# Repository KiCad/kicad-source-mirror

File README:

= KiCad GUI translations

This is the repository for the po files that is used for the GUI
translations for KiCad.

It is cmake equipped to conform with the rest of the installation
principles for KiCad.

== Depends
- Cmake
- Gettext

== How to install
```
cd kicad-i18n
cmake .
make
make install
```

If you want to change the default install prefix to match your KiCad
build, you can add for
example use `-DCMAKE_INSTALL_PREFIX=/usr`.

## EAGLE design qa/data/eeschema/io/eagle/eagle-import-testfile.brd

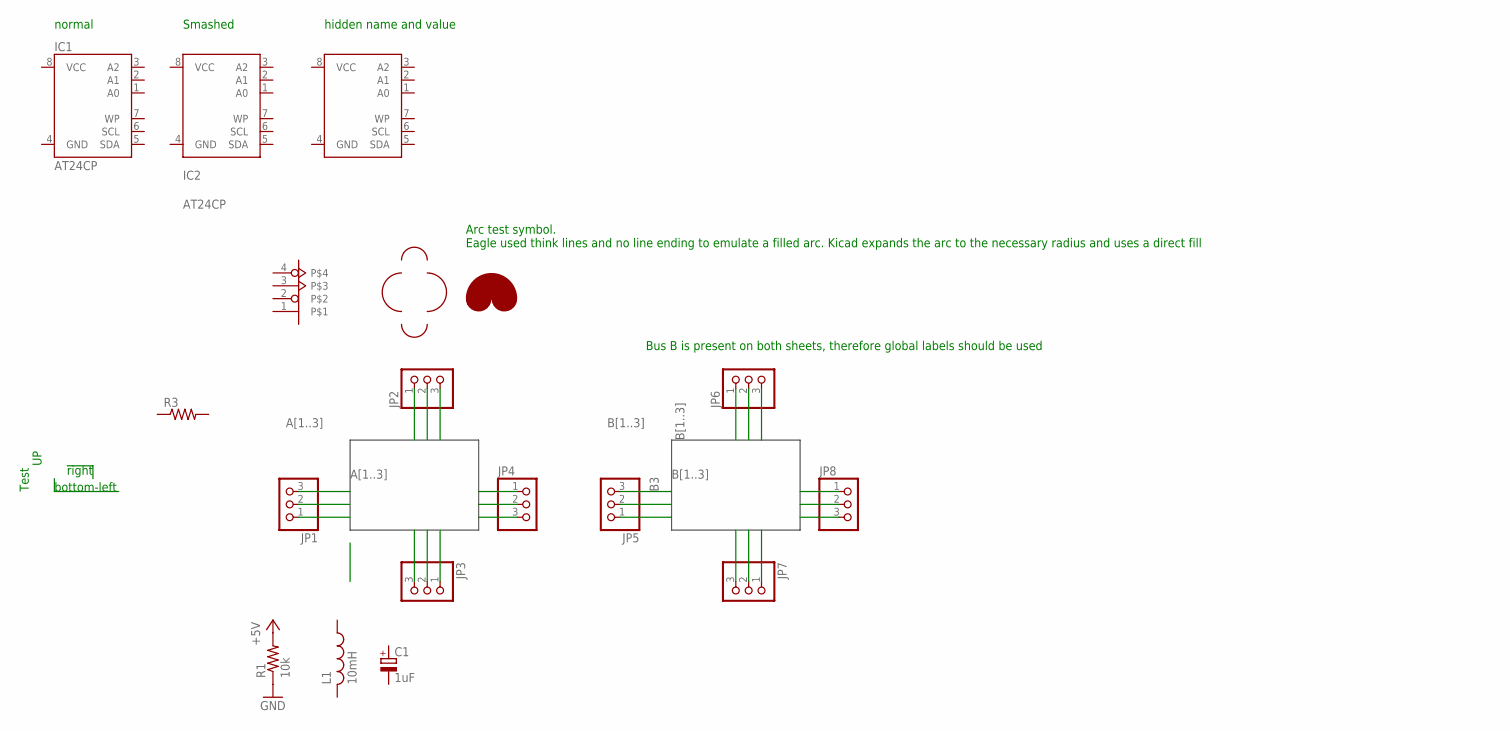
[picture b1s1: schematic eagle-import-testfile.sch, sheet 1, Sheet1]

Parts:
C1: 1uF; 085CS_1AR
IC1, IC2, IC3: AT24CP; DIL08
JP1, JP2, JP3, JP4, JP5, JP6, JP7, JP8: PINHD-1X3; 1X03
L1: 10mH; L2012C
R1: 10k; R0603
R3: R-US_0204/2V; 0204V
U$2: PINSHAPETEST; 1X04

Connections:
+5V: R1.2
A1: JP1.1, JP2.1, JP3.1, JP4.1
A2: JP1.2, JP2.2, JP3.2, JP4.2
A3: JP1.3, JP2.3, JP3.3, JP4.3
B1: JP5.1, JP6.1, JP7.3, JP8.1; also elsewhere on the board
B2: JP5.2, JP6.2, JP7.2, JP8.2; also elsewhere on the board
B3: JP5.3, JP6.3, JP7.1, JP8.3; also elsewhere on the board
GND: IC1.4 (GND), IC2.4 (GND), IC3.4 (GND), R1.1
VCC: IC1.8 (VCC), IC2.8 (VCC), IC3.8 (VCC)

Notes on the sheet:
right
Test
bottom-left
Bus B is present on both sheets, therefore global labels should be used
Arc test symbol. Eagle used think lines and no line ending to emulate a filled arc. Kicad expands the arc to the necessary radius and uses a direct fill
normal
Smashed
hidden name and value

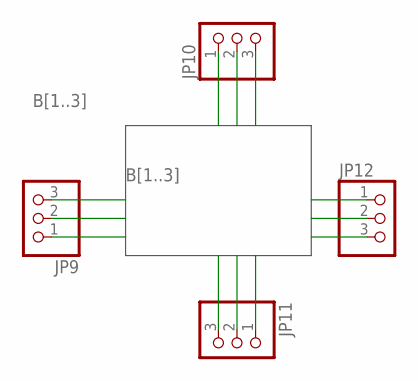
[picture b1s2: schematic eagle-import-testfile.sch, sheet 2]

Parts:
JP9, JP10, JP11, JP12: PINHD-1X3; 1X03

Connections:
B1: JP9.1, JP10.1, JP11.3, JP12.1; also elsewhere on the board
B2: JP9.2, JP10.2, JP11.2, JP12.2; also elsewhere on the board
B3: JP9.3, JP10.3, JP11.1, JP12.3; also elsewhere on the board

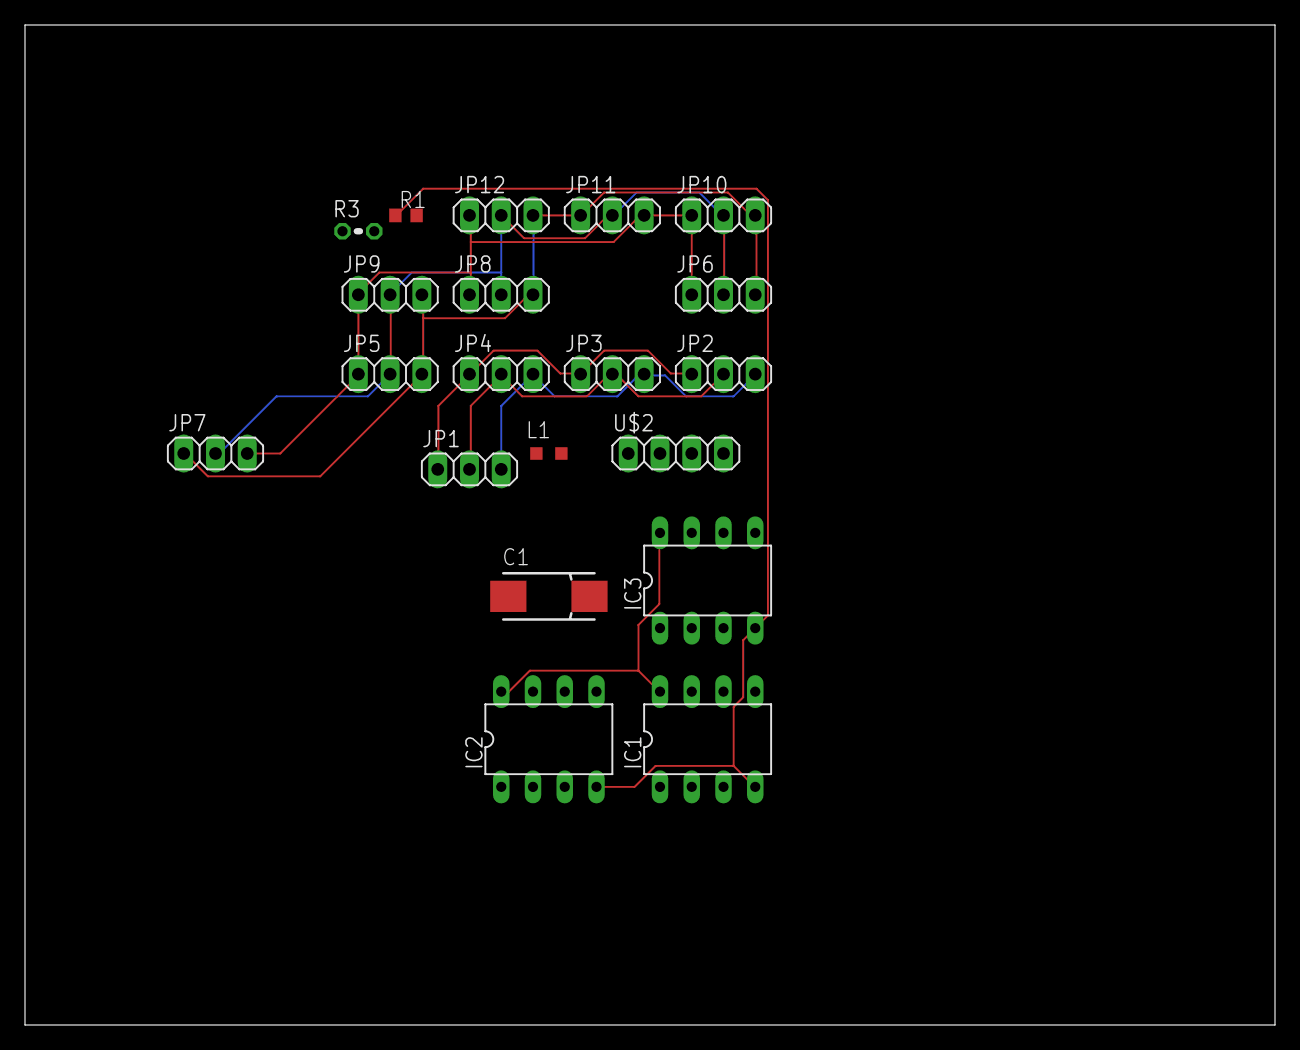
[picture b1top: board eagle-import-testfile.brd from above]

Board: 2 copper layers, 100.0 x 80.0 mm, 20 parts (0 on the bottom side), 8 nets.

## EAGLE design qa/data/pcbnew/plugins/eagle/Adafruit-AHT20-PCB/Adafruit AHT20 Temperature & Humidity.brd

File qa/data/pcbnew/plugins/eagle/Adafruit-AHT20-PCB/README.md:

## Adafruit AHT20 Temperature and Humidity Sensor PCB

<a href="http://www.adafruit.com/products/4566"><br/>
Click here to purchase one from the Adafruit shop</a>

PCB files for the Adafruit AHT20 Temperature and Humidity Sensor.

Format is EagleCAD schematic and board layout
* https://www.adafruit.com/product/4566

### Description

The AHT20 is a nice but inexpensive temperature and humidity sensor from the same folks that brought us the DHT22. You can take sensor readings as often as you like, and it uses standard I2C so its super easy to use with any Arduino or Linux/Raspberry Pi board.

This sensor has a typical accuracy of +- 2% relative humidity, and +-0.3 °C. There is only one I2C address so its not a good option when you need multiple humidity sensors.

As with all Adafruit breakouts, we've done the work to make this handy temperature-and-humidity super easy to use. We've put it on a breakout board with the required support circuitry and connectors to make it easy to work with and is now a trend we've added SparkFun Qwiic compatible STEMMA QT JST SH connectors that allow you to get going without needing to solder. Just use a STEMMA QT adapter cable, plug it into your favorite microcontroller or Blinka supported SBC and you're ready to rock!

### License

Adafruit invests time and resources providing this open source design, please support Adafruit and open-source hardware by purchasing products from [Adafruit](https://www.adafruit.com)!

Designed by Limor Fried/Ladyada for Adafruit Industries.

Creative Commons Attribution/Share-Alike, all text above must be included in any redistribution.
See license.txt for additional details.

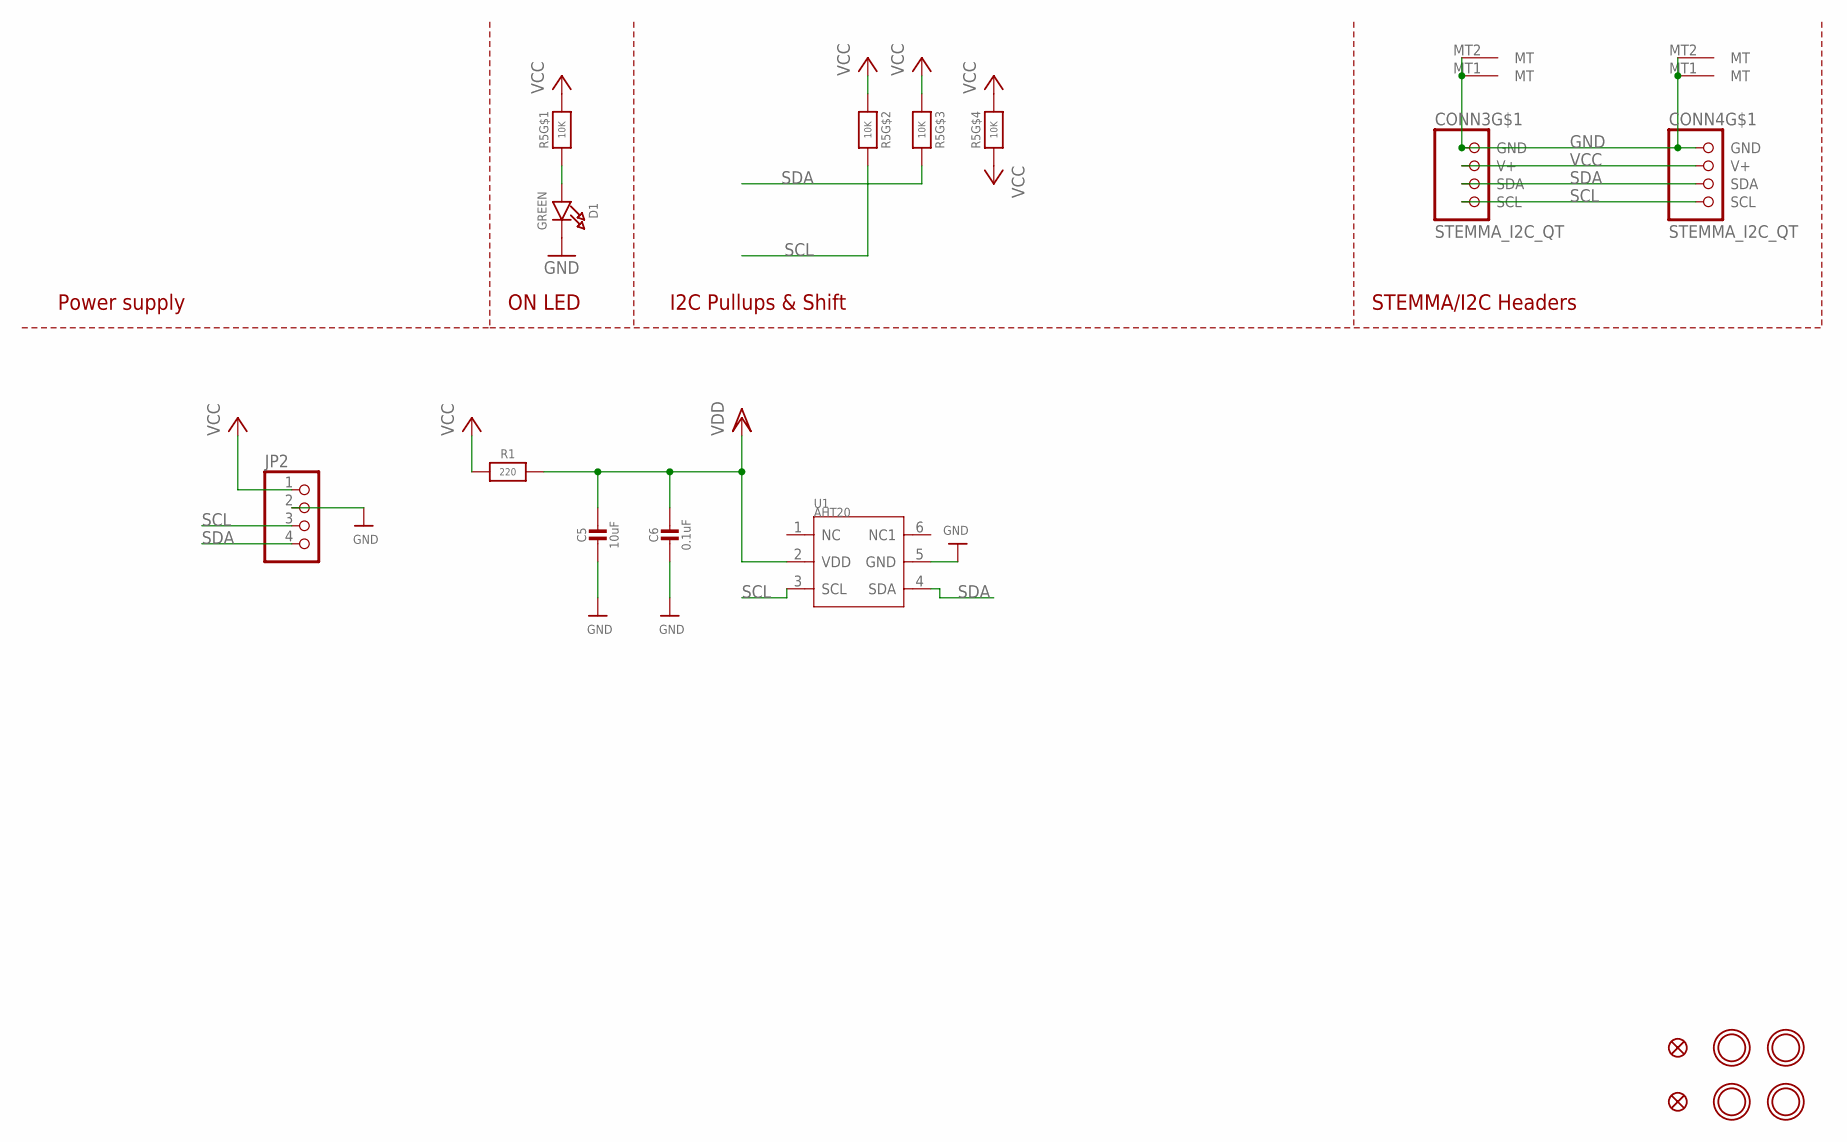
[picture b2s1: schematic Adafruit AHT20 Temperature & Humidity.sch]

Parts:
C5: 10uF; 0805-NO
C6: 0.1uF; 0603-NO
CONN3, CONN4: STEMMA_I2C_QT; JST_SH4
D1: GREEN; CHIPLED_0603_NOOUTLINE
FID3, FID4: FIDUCIAL_1MM
JP2: HEADER-1X476MIL; 1X04_ROUND_76
R1: 220; 0603-NO
R5: 10K; RESPACK_4X0603
U1: AHT20; SNR6-1.0-3X3X1MM
U$19, U$20, U$22, U$25: MOUNTINGHOLE2.5; MOUNTINGHOLE_2.5_PLATED

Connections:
GND: C5.2, C6.2, CONN3.1 (GND), CONN3.MT1 (MT), CONN3.MT2 (MT), CONN4.1 (GND), CONN4.MT1 (MT), CONN4.MT2 (MT), D1.C, JP2.2, U1.5 (GND)
unnamed: D1.A, R5.1
SCL: CONN3.4 (SCL), CONN4.4 (SCL), JP2.3, R5.7 (2), U1.3 (SCL)
SDA: CONN3.3 (SDA), CONN4.3 (SDA), JP2.4, R5.6 (2), U1.4 (SDA)
VCC: CONN3.2 (V+), CONN4.2 (V+), JP2.1, R1.1, R5.2 (1), R5.3 (1), R5.4 (1), R5.5 (2), R5.8 (2)
VDD: C5.1, C6.1, R1.2, U1.2 (VDD)

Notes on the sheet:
I2C Pullups & Shift
STEMMA/I2C Headers
ON LED
Power supply

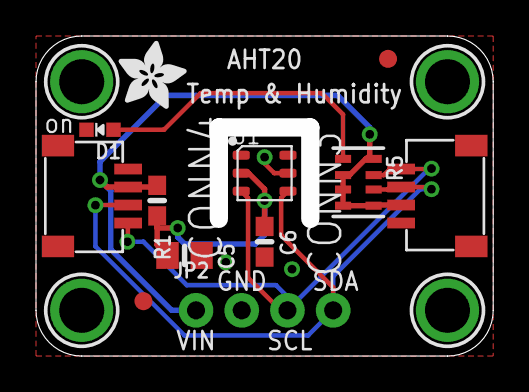
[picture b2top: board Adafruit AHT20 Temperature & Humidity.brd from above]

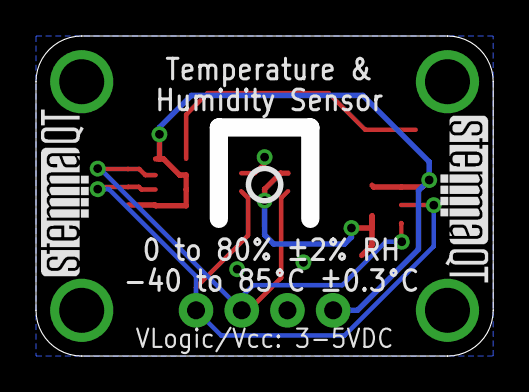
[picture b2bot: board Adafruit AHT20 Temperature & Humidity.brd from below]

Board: 2 copper layers, 25.4 x 17.8 mm, 19 parts (3 on the bottom side), 6 nets.

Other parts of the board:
U$28: ADAFRUIT_3.5MM
U$29: PCBFEAT-REV-040
U$30, U$31: STEMMAQT

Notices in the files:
parts and their libraries:
microbuilder: This work is placed in the public domain, and may be freely used for commercial and non-commercial work with the following conditions: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
